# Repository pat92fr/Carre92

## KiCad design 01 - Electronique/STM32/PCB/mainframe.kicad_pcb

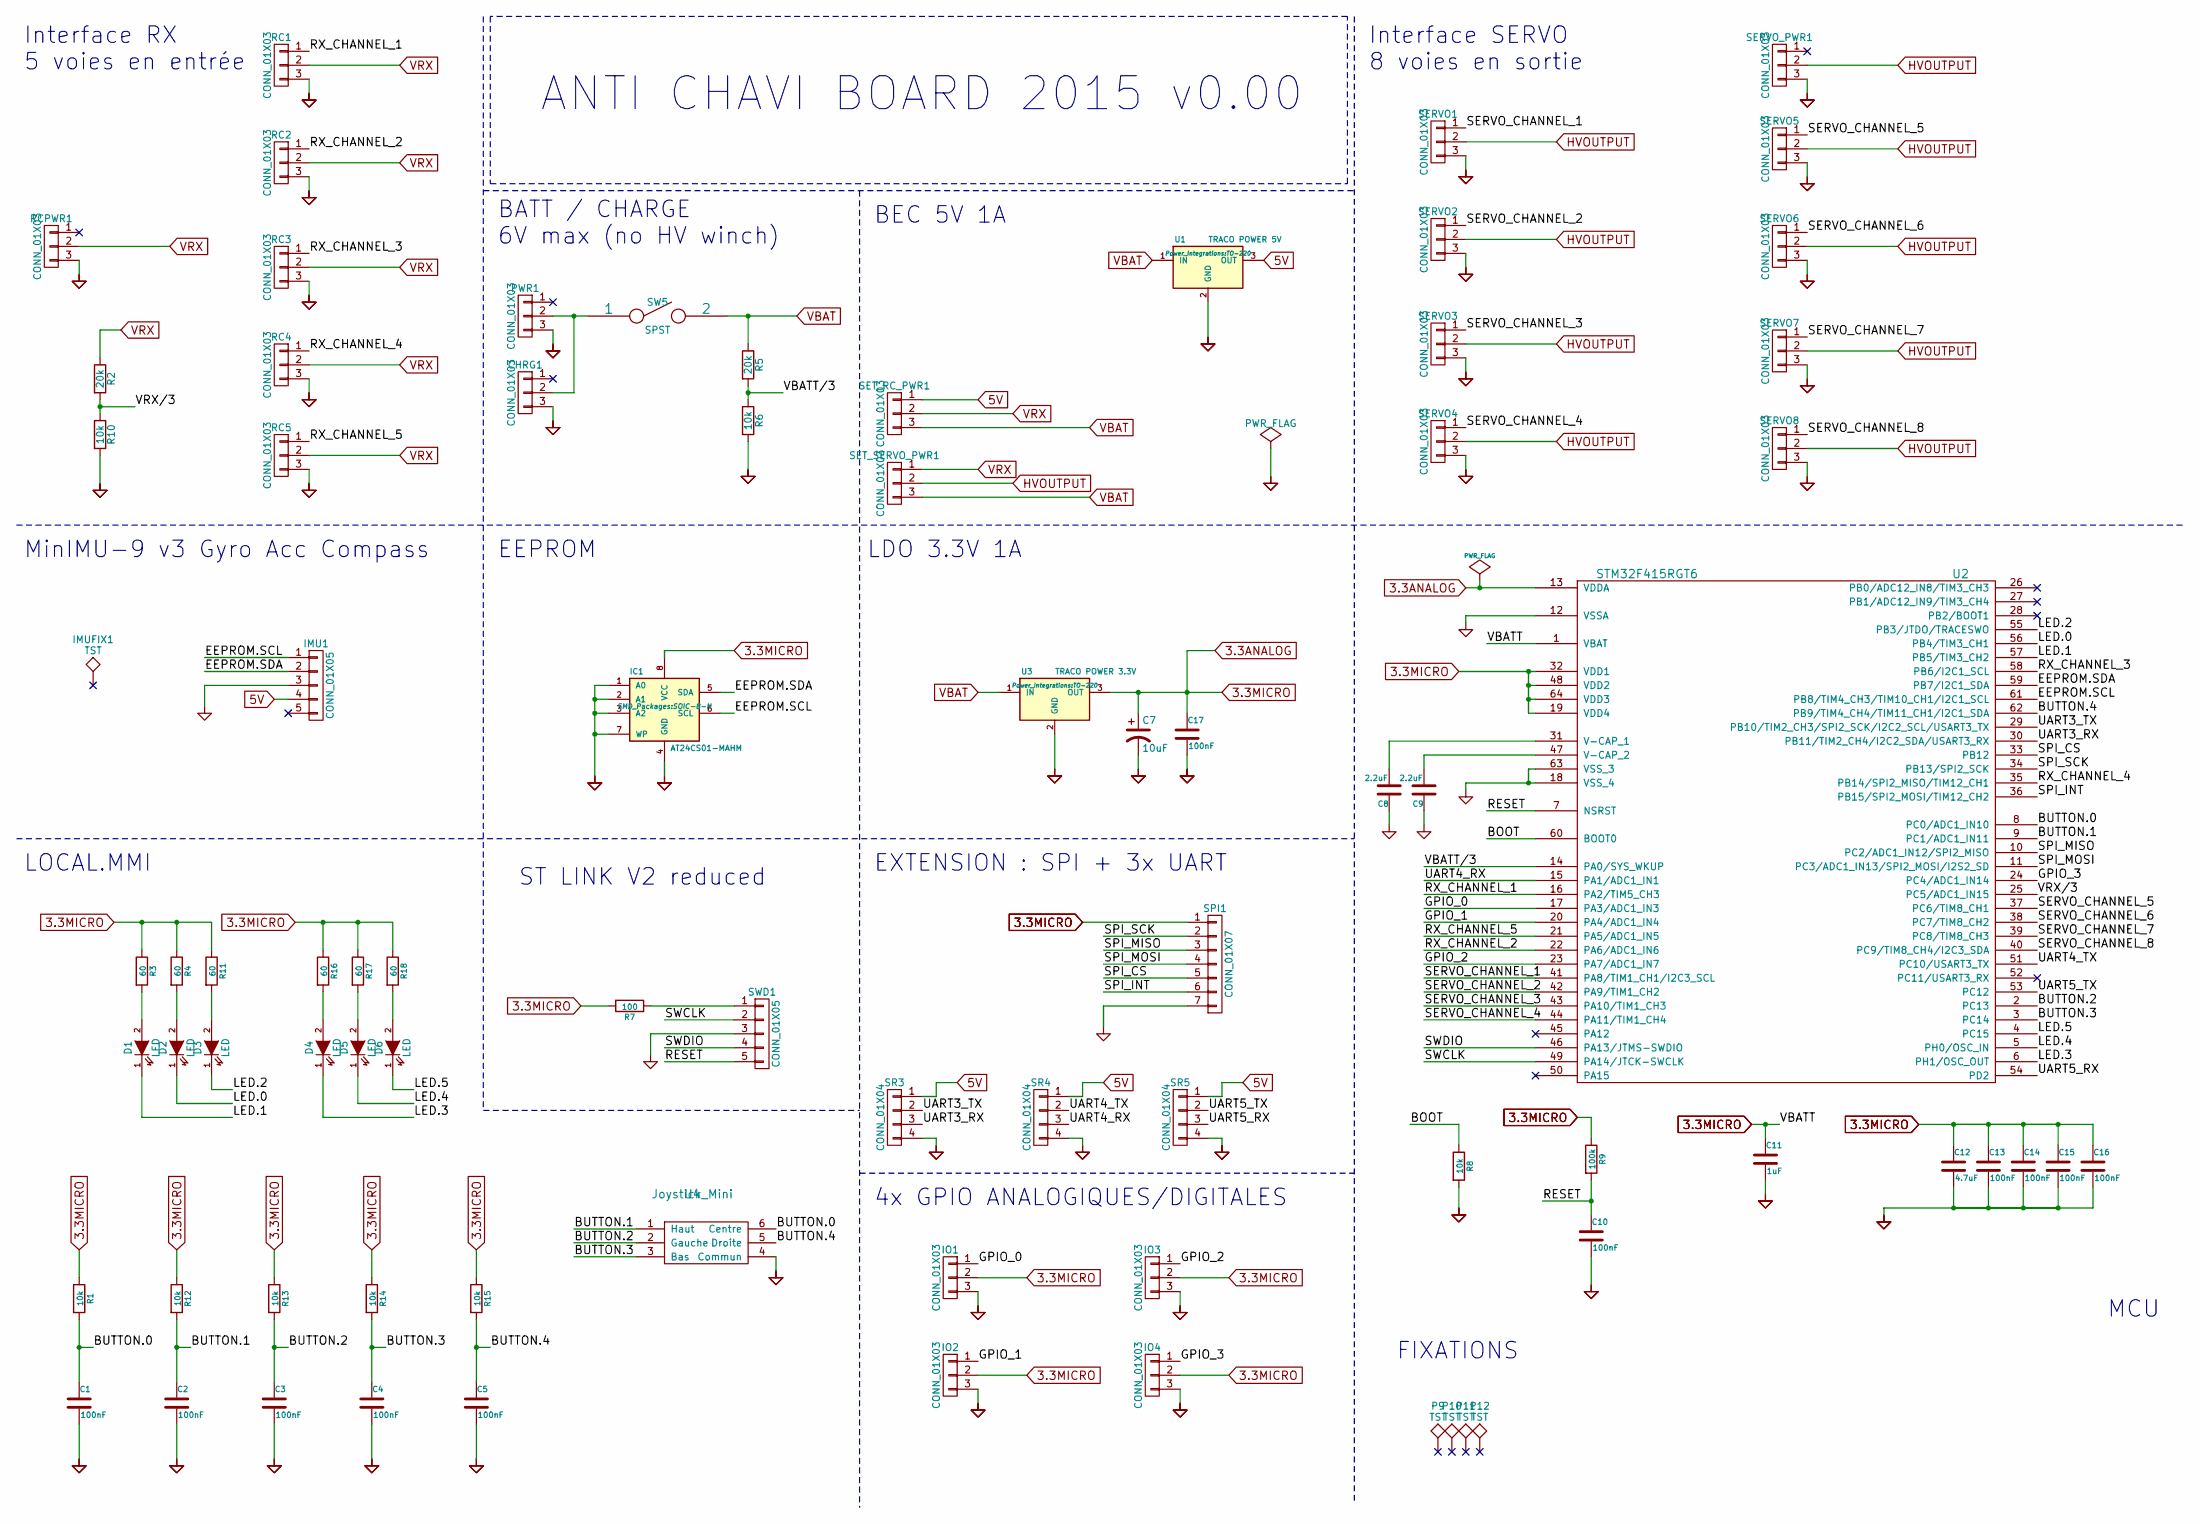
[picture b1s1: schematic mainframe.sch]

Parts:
C1, C2, C3, C4, C5, C10, C13, C14, C15, C16, C17: 100nF; C_0603_HandSoldering
C7: 10uF; C_0805_HandSoldering
C8, C9: 2.2uF; C_0603_HandSoldering
C11: 1uF; C_0603_HandSoldering
C12: 4.7uF; C_0603_HandSoldering
CHRG1: CONN_01X03; Pin_Header_Straight_1x03
D1, D2, D3, D4, D5, D6: LED; LED-0805
IC1: AT24CS01-MAHM; SOIC-8-N
IMU1: CONN_01X05; Pin_Header_Straight_1x05
IMUFIX1: TST; 1pin
IO1, IO2, IO3, IO4: CONN_01X03; Pin_Header_Straight_1x03
P9, P10, P11, P12: TST; 1pin
PWR1: CONN_01X03; Pin_Header_Straight_1x03
R1, R6, R8, R10, R12, R13, R14, R15: 10k; R_0603_HandSoldering
R2, R5: 20k; R_0603_HandSoldering
R3, R4, R11, R16, R17, R18: 60; R_0603_HandSoldering
R7: 100; R_0603_HandSoldering
R9: 100k; R_0603_HandSoldering
RC1, RC2, RC3, RC4, RC5: CONN_01X03; Pin_Header_Straight_1x03
RCPWR1: CONN_01X03; Pin_Header_Straight_1x03
SERVO1, SERVO2, SERVO3, SERVO4, SERVO5, SERVO6, SERVO7, SERVO8: CONN_01X03; Pin_Header_Straight_1x03
SERVO_PWR1: CONN_01X03; Pin_Header_Straight_1x03
SET_RC_PWR1: CONN_01X03; Pin_Header_Straight_1x03
SET_SERVO_PWR1: CONN_01X03; Pin_Header_Straight_1x03
SPI1: CONN_01X07; Pin_Header_Straight_1x07
SR3, SR4, SR5: CONN_01X04; Pin_Header_Straight_1x04
SW5: SPST; Pin_Header_Straight_1x02
SWD1: CONN_01X05; Pin_Header_Straight_1x05
U1: TRACO POWER 5V; TO-220
U2: STM32F415RGT6; LQFP-64_10x10mm_Pitch0.5mm
U3: TRACO POWER 3.3V; TO-220
U4: Joystick_Mini

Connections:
3.3ANALOG: C7.1, C11.1, C12.1, C13.1, C14.1, C15.1, C16.1, C17.1, IC1.8 (VCC), IO1.2, IO2.2, IO3.2, IO4.2, R1.1, R3.1, R4.1, R7.2, R9.1, R11.1, R12.1, R13.1, R14.1, R15.1, R16.1, R17.1, R18.1, SPI1.1, U2.1 (VBAT), U2.13 (VDDA), U2.19 (VDD4), U2.32 (VDD1), U2.48 (VDD2), U2.64 (VDD3), U3.3 (OUT)
5V: IMU1.4, SET_RC_PWR1.1, SR3.1, SR4.1, SR5.1, U1.3 (OUT)
/BOOT: R8.1, U2.60 (BOOT0)
/BUTTON.0: C1.1, R1.2, U2.8 (PC0/ADC1_IN10), U4.6 (Centre)
/BUTTON.1: C2.1, R12.2, U2.9 (PC1/ADC1_IN11), U4.1 (Haut)
/BUTTON.2: C3.1, R13.2, U2.2 (PC13), U4.2 (Gauche)
/BUTTON.3: C4.1, R14.2, U2.3 (PC14), U4.3 (Bas)
/BUTTON.4: C5.1, R15.2, U2.62 (PB9/TIM4_CH4/TIM11_CH1/I2C1_SDA), U4.5 (Droite)
/EEPROM.SCL: IC1.6 (SCL), IMU1.1, U2.61 (PB8/TIM4_CH3/TIM10_CH1/I2C1_SCL)
/EEPROM.SDA: IC1.5 (SDA), IMU1.2, U2.59 (PB7/I2C1_SDA)
/GPIO_0: IO1.1, U2.17 (PA3/ADC1_IN3)
/GPIO_1: IO2.1, U2.20 (PA4/ADC1_IN4)
/GPIO_2: IO3.1, U2.23 (PA7/ADC1_IN7)
/GPIO_3: IO4.1, U2.24 (PC4/ADC1_IN14)
/LED.0: D2.1 (K), U2.56 (PB4/TIM3_CH1)
/LED.1: D1.1 (K), U2.57 (PB5/TIM3_CH2)
/LED.2: D3.1 (K), U2.55 (PB3/JTDO/TRACESWO)
/LED.3: D4.1 (K), U2.6 (PH1/OSC_OUT)
/LED.4: D5.1 (K), U2.5 (PH0/OSC_IN)
/LED.5: D6.1 (K), U2.4 (PC15)
/RESET: C10.1, R9.2, SWD1.5, U2.7 (NSRST)
/RX_CHANNEL_1: RC1.1, U2.16 (PA2/TIM5_CH3)
/RX_CHANNEL_2: RC2.1, U2.22 (PA6/ADC1_IN6)
/RX_CHANNEL_3: RC3.1, U2.58 (PB6/I2C1_SCL)
/RX_CHANNEL_4: RC4.1, U2.35 (PB14/SPI2_MISO/TIM12_CH1)
/RX_CHANNEL_5: RC5.1, U2.21 (PA5/ADC1_IN5)
/SERVO_CHANNEL_1: SERVO1.1, U2.41 (PA8/TIM1_CH1/I2C3_SCL)
/SERVO_CHANNEL_2: SERVO2.1, U2.42 (PA9/TIM1_CH2)
/SERVO_CHANNEL_3: SERVO3.1, U2.43 (PA10/TIM1_CH3)
/SERVO_CHANNEL_4: SERVO4.1, U2.44 (PA11/TIM1_CH4)
/SERVO_CHANNEL_5: SERVO5.1, U2.37 (PC6/TIM8_CH1)
/SERVO_CHANNEL_6: SERVO6.1, U2.38 (PC7/TIM8_CH2)
/SERVO_CHANNEL_7: SERVO7.1, U2.39 (PC8/TIM8_CH3)
/SERVO_CHANNEL_8: SERVO8.1, U2.40 (PC9/TIM8_CH4/I2C3_SDA)
/SPI_CS: SPI1.5, U2.33 (PB12)
/SPI_INT: SPI1.6, U2.36 (PB15/SPI2_MOSI/TIM12_CH2)
/SPI_MISO: SPI1.3, U2.10 (PC2/ADC1_IN12/SPI2_MISO)
/SPI_MOSI: SPI1.4, U2.11 (PC3/ADC1_IN13/SPI2_MOSI/I2S2_SD)
/SPI_SCK: SPI1.2, U2.34 (PB13/SPI2_SCK)
/SWCLK: SWD1.2, U2.49 (PA14/JTCK-SWCLK)
/SWDIO: SWD1.4, U2.46 (PA13/JTMS-SWDIO)
/UART3_RX: SR3.3, U2.30 (PB11/TIM2_CH4/I2C2_SDA/USART3_RX)
/UART3_TX: SR3.2, U2.29 (PB10/TIM2_CH3/SPI2_SCK/I2C2_SCL/USART3_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)
/UART4_RX: SR4.3, U2.15 (PA1/ADC1_IN1)
/UART4_TX: SR4.2, U2.51 (PC10/USART3_TX)
/UART5_RX: SR5.3, U2.54 (PD2)
/UART5_TX: SR5.2, U2.53 (PC12)
/VBATT/3: R5.2, R6.1, U2.14 (PA0/SYS_WKUP)
/VRX/3: R2.2, R10.1, U2.25 (PC5/ADC1_IN15)
GND: C1.2, C2.2, C3.2, C4.2, C5.2, C7.2, C8.1, C9.1, C10.2, C11.2, C12.2, C13.2, C14.2, C15.2, C16.2, C17.2, CHRG1.3, IC1.1 (A0), IC1.2 (A1), IC1.3 (A2), IC1.4 (GND), IC1.7 (WP), IMU1.3, IO1.3, IO2.3, IO3.3, IO4.3, PWR1.3, R6.2, R8.2, R10.2, RC1.3, RC2.3, RC3.3, RC4.3, RC5.3, RCPWR1.3, SERVO1.3, SERVO2.3, SERVO3.3, SERVO4.3, SERVO5.3, SERVO6.3, SERVO7.3, SERVO8.3, SERVO_PWR1.3, SPI1.7, SR3.4, SR4.4, SR5.4, SWD1.3, U1.2 (GND), U2.12 (VSSA), U2.18 (VSS_4), U2.63 (VSS_3), U3.2 (GND), U4.4 (Commun)
HVOUTPUT: SERVO1.2, SERVO2.2, SERVO3.2, SERVO4.2, SERVO5.2, SERVO6.2, SERVO7.2, SERVO8.2, SERVO_PWR1.2, SET_SERVO_PWR1.2
unnamed: C8.2, U2.31 (V-CAP_1)
unnamed: C9.2, U2.47 (V-CAP_2)
unnamed: CHRG1.2, PWR1.2, SW5.1
unnamed: D1.2 (A), R3.2
unnamed: D2.2 (A), R4.2
unnamed: D3.2 (A), R11.2
unnamed: D4.2 (A), R16.2
unnamed: D5.2 (A), R17.2
unnamed: D6.2 (A), R18.2
unnamed: R7.1, SWD1.1
VBAT: R5.1, SET_RC_PWR1.3, SET_SERVO_PWR1.3, SW5.2, U1.1 (IN), U3.1 (IN)
VRX: R2.1, RC1.2, RC2.2, RC3.2, RC4.2, RC5.2, RCPWR1.2, SET_RC_PWR1.2, SET_SERVO_PWR1.1

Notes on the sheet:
MinIMU-9 v3 Gyro Acc Compass
LOCAL.MMI
EEPROM
MCU
ST LINK V2 reduced
ANTI CHAVI BOARD 2015 v0.00
BATT / CHARGE 6V max (no HV winch)
Interface RX 5 voies en entrée
Interface SERVO 8 voies en sortie
EXTENSION : SPI + 3x UART
4x GPIO ANALOGIQUES/DIGITALES
FIXATIONS
BEC 5V 1A
LDO 3.3V 1A

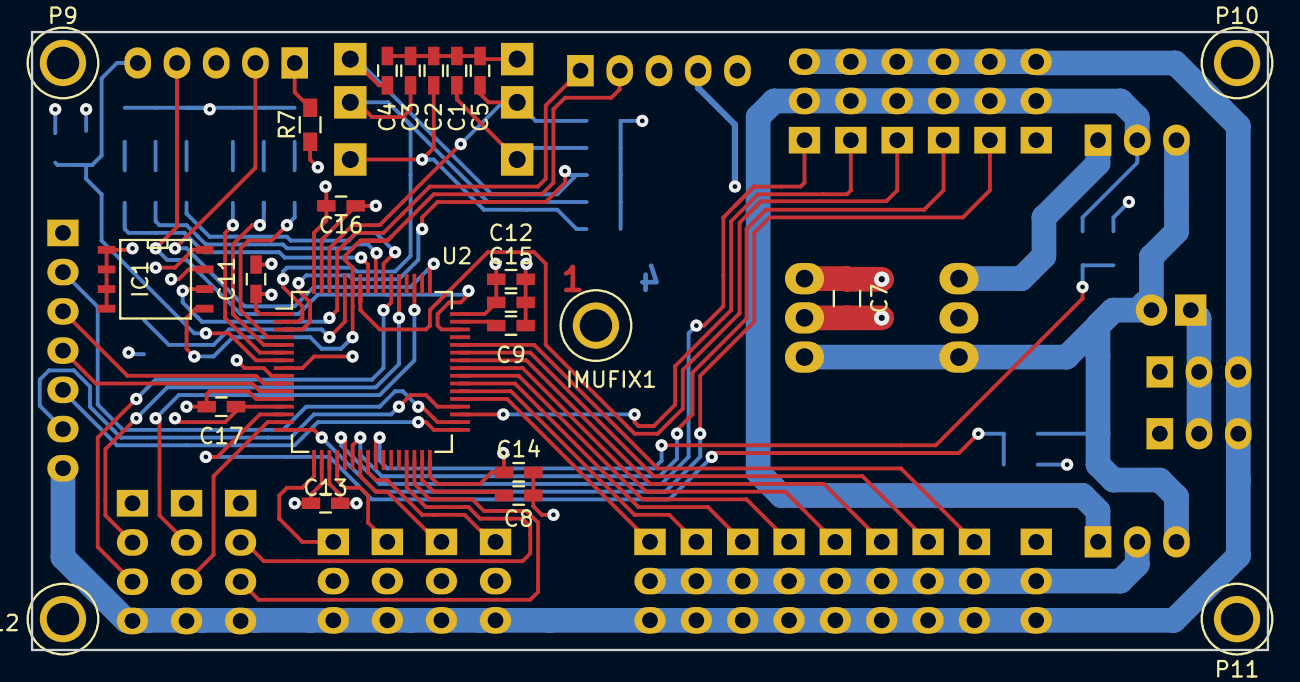
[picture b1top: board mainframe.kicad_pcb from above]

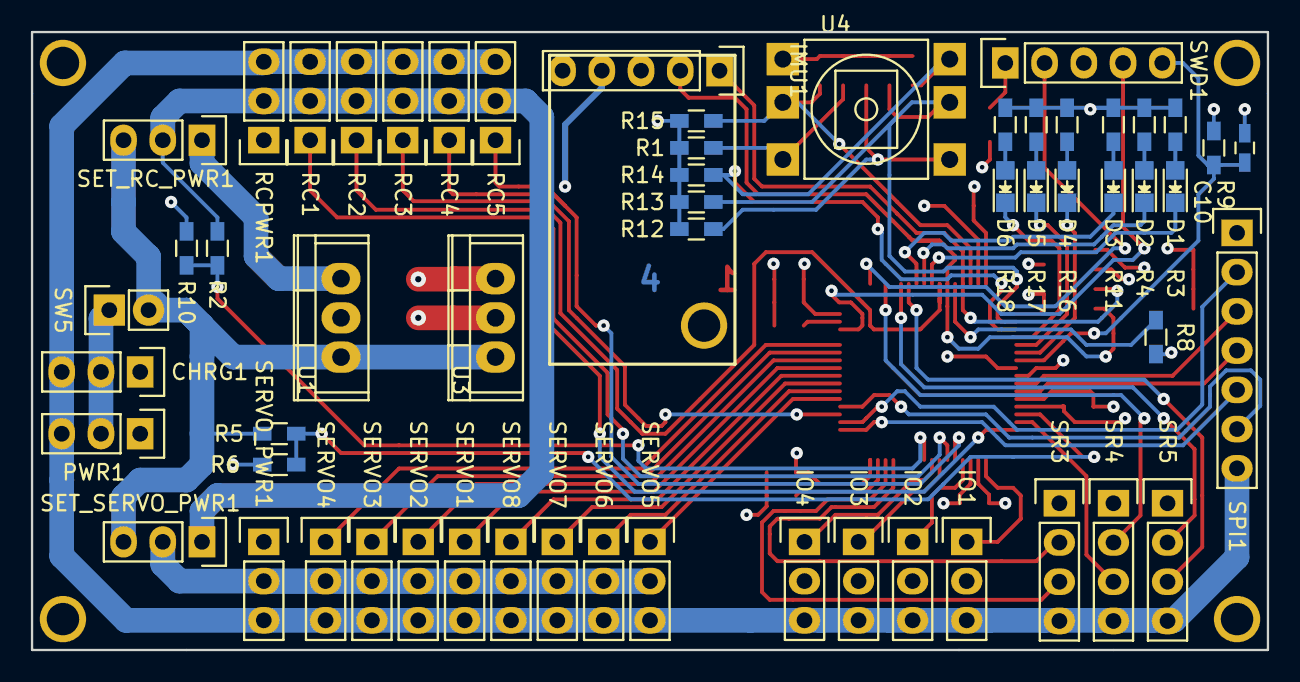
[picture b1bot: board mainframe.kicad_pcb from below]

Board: 4 copper layers, 80.0 x 40.0 mm, 80 parts (57 on the bottom side), 63 nets.

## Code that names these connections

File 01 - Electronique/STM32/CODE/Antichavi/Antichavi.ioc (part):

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Mcu.Name=STM32F415RGTx
Mcu.Package=LQFP64
Mcu.UserName=STM32F415RGTx
PA0-WKUP.GPIOParameters=GPIO_Label
PA0-WKUP.GPIO_Label=VBATT_DIV_3
PA0-WKUP.Signal=ADCx_IN0
PA1.Mode=Asynchronous
PA1.Signal=UART4_RX
PA10.GPIOParameters=GPIO_Label
PA10.GPIO_Label=SERVO_CHANNEL_3
PA10.Signal=S_TIM1_CH3
PA11.GPIOParameters=GPIO_Label
PA11.GPIO_Label=SERVO_CHANNEL_4
PA11.Signal=S_TIM1_CH4
PA13.Mode=Serial-Wire
PA13.Signal=SYS_JTMS-SWDIO
PA14.Mode=Serial-Wire
PA14.Signal=SYS_JTCK-SWCLK
PA2.GPIOParameters=GPIO_Label
PA2.GPIO_Label=RX_CHANNEL_1
PA2.Signal=S_TIM9_CH1
PA3.GPIOParameters=GPIO_Label
PA3.GPIO_Label=GPIO_0
PA3.Signal=GPIO_Input
PA4.GPIOParameters=GPIO_Label
PA4.GPIO_Label=GPIO_4
PA4.Signal=GPIO_Input
PA5.GPIOParameters=GPIO_Label
PA5.GPIO_Label=RX_CHANNEL_5
PA5.Signal=S_TIM2_CH1_ETR
PA6.GPIOParameters=GPIO_Label
PA6.GPIO_Label=RX_CHANNEL_2
PA6.Signal=S_TIM3_CH1
PA7.GPIOParameters=GPIO_Label
PA7.GPIO_Label=GPIO_2
PA7.Signal=GPIO_Input
PA8.GPIOParameters=GPIO_Label
PA8.GPIO_Label=SERVO_CHANNEL_1
PA8.Signal=S_TIM1_CH1
PA9.GPIOParameters=GPIO_Label
PA9.GPIO_Label=SERVO_CHANNEL_2
PA9.Signal=S_TIM1_CH2
PB10.Mode=Asynchronous
PB10.Signal=USART3_TX
PB11.Mode=Asynchronous
PB11.Signal=USART3_RX
PB12.GPIOParameters=GPIO_Label
PB12.GPIO_Label=SPI_CS
PB12.Signal=GPIO_Output
PB13.Mode=Full_Duplex_Master
PB13.Signal=SPI2_SCK
PB14.GPIOParameters=GPIO_Label
PB14.GPIO_Label=RX_CHANNEL_4
PB14.Signal=S_TIM12_CH1
PB15.GPIOParameters=GPIO_Label
PB15.GPIO_Label=SPI_INT
PB15.Signal=GPXTI15
PB3.GPIOParameters=GPIO_Label
PB3.GPIO_Label=LED2
PB3.Signal=GPIO_Output
PB4.GPIOParameters=GPIO_Label
PB4.GPIO_Label=LED0
PB4.Signal=GPIO_Output
PB5.GPIOParameters=GPIO_Label
PB5.GPIO_Label=LED1
PB5.Signal=GPIO_Output
PB6.GPIOParameters=GPIO_Label
PB6.GPIO_Label=RX_CHANNEL_3
PB6.Signal=S_TIM4_CH1
PB7.Mode=I2C
PB7.Signal=I2C1_SDA
PB8.Mode=I2C
PB8.Signal=I2C1_SCL
PB9.GPIOParameters=GPIO_Label
PB9.GPIO_Label=BUTTON_4
PB9.Signal=GPXTI9
PC0.GPIOParameters=GPIO_Label
PC0.GPIO_Label=BUTTON_0
PC0.Signal=GPXTI0
PC1.GPIOParameters=GPIO_Label
PC1.GPIO_Label=BUTTON_1
PC1.Signal=GPXTI1
PC10.Mode=Asynchronous
PC10.Signal=UART4_TX
PC12.Mode=Asynchronous
PC12.Signal=UART5_TX
PC13-ANTI_TAMP.GPIOParameters=GPIO_Label
PC13-ANTI_TAMP.GPIO_Label=BUTTON_2
PC13-ANTI_TAMP.Signal=GPXTI13
PC14-OSC32_IN.GPIOParameters=GPIO_Label
PC14-OSC32_IN.GPIO_Label=BUTTON_3
PC14-OSC32_IN.Signal=GPXTI14
PC15-OSC32_OUT.GPIOParameters=GPIO_Label
PC15-OSC32_OUT.GPIO_Label=LED5
PC15-OSC32_OUT.Signal=GPIO_Output
PC2.Mode=Full_Duplex_Master
PC2.Signal=SPI2_MISO
PC3.Mode=Full_Duplex_Master
PC3.Signal=SPI2_MOSI
PC4.GPIOParameters=GPIO_Label
PC4.GPIO_Label=GPIO_3
PC4.Signal=GPIO_Input
PC5.GPIOParameters=GPIO_Label
PC5.GPIO_Label=VRX_DIV_3
PC5.Signal=ADCx_IN15
PC6.GPIOParameters=GPIO_Label
PC6.GPIO_Label=SERVO_CHANNEL_5
PC6.Signal=S_TIM8_CH1
PC7.GPIOParameters=GPIO_Label
PC7.GPIO_Label=SERVO_CHANNEL_6
PC7.Signal=S_TIM8_CH2
PC8.GPIOParameters=GPIO_Label
PC8.GPIO_Label=SERVO_CHANNEL_7
PC8.Signal=S_TIM8_CH3
PC9.GPIOParameters=GPIO_Label
PC9.GPIO_Label=SERVO_CHANNEL_8
PC9.Signal=S_TIM8_CH4
PD2.Mode=Asynchronous
PD2.Signal=UART5_RX
PH0-OSC_IN.GPIOParameters=GPIO_Label
PH0-OSC_IN.GPIO_Label=LED4
PH0-OSC_IN.Signal=GPIO_Output
PH1-OSC_OUT.GPIOParameters=GPIO_Label
PH1-OSC_OUT.GPIO_Label=LED3
PH1-OSC_OUT.Signal=GPIO_Output
RCC.HSE_VALUE=25000000
RCC.SYSCLKFreq_VALUE=168000000
RCC.SYSCLKSource=RCC_SYSCLKSOURCE_PLLCLK
board=Antichavi
boardIOC=true

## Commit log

2019-07-18 AIv1
2019-07-19 Serial Code
2019-07-19 Example IA
2019-07-19 STM32F415_ctrl
2019-07-19 servo INV
2019-07-19 RX CH1 CH2 bypass OK
2019-07-19 Commutation A/M
2019-07-19 RX circular FIX
2019-07-20 FSM add
2019-07-20 PWM Input capture filter FIX + BT_COM
2019-07-20 Coffret Ctrl
2019-07-21 Coffret Ctrl MAJ
2019-07-23 logo
2019-07-24 AI V2
2019-07-25 CNN linear
2019-07-25 AI2 test 3 bitume
2019-07-26 test4 bitume
2019-07-27 CNN up
2019-07-28 CNN v2 MAJ
2019-07-28 AIv2 Bitume MAJ
2019-07-28 Script de génération du dataset
    Script de génération du dataset et photos de fond
2019-07-29 Update GenereImages.py
    Modification de l'arborescence du dataset : un répertoire par image de fond puis 1 répertoire par angle d'orientation de la ligne.
    Sinon, plusieurs centaines de milliers de fichiers dans un répertoire, c'est difficile à gérer !
2019-07-29 Update GenereImages.py
    Modification des répertoires pour stocker les images
2019-07-30 AI v2 Vizu
2019-07-30 Update GenereImages.py
    Optimisation et parallélisation des calculs.
    Calcule le nombre de coeurs (OK sous Windows, pour linuxn modifier les lignes 132-135) et lance n calculs en parallèle.
2019-07-30 IA v2
2019-07-31 cli test
2019-07-31 BackUp rover
2019-08-01 Full CONV test
2019-08-07 test CLI
2019-08-07 STM32 direction active AI
2019-08-07 STM32 RC start AI (robust)
2019-08-07 Alain V2
2019-08-08 Alain Fond
2019-08-08 Alain script
2019-08-08 fonds
2019-08-09 Benjamin
2019-08-09 IAv3
2019-08-09 CleanUP
2019-08-09 Pipeline
2019-08-09 Predict
2019-08-11 datagenerator
2019-08-11 Pipeline no more X Y dataset file
2019-08-11 Pipeline v1 ok
2019-08-12 Dataset prédiction
2019-08-12 Buggy
2019-08-13 ANN prediction
2019-08-13 tt01
2019-08-14 Prediction
2019-08-15 Camera v2 avec Buggy server et client update
2019-08-15 client
2019-08-15 Notes démarrage Jetson
    Quelques notes sur l'optimisation du temps de démarrage et comment lancer un script automatiquement et le plus tôt possible.
2019-08-16 PCB upload
2019-08-16 STM32 Soft : ajout des lidars
2019-08-16 STM32
2019-08-17 STM32
    Permutation des UART. Ne marche pas mieux. Time out 3 seconde coté Python.
2019-08-17 STM32 fix IRQ
    Correction inversion UART LiD et LiG
2019-08-17 STM32 refactoring
    types, enum, telemetry stop and wait,
    fix on Telemetry frame reply per AI frame
2019-08-17 test serial comm between jetson and STM32
2019-08-17 LIDAR OK REady for PID with Jetson
2019-08-19 Lidar PID
2019-08-20 Telemetry et PID Wall
2019-08-20 Config file buggy
2019-08-20 prediction 5x5x1
2019-08-21 PID simplification
2019-08-21 Buggy client server ( Bernard v1 )
2019-08-21 Reglages mono PID, vitesse manuelle
2019-08-21 TODOs
2019-08-22 Ajout START/STOP
2019-08-22 Stupid speed regulation in AUTO mode
2019-08-22 Speed improvement
2019-08-22 todo
2019-08-22 Telemetry
2019-08-23 Régulation de vitesse et dual rate direction
2019-08-23 Telemetry merge
2019-08-23 Essais avec telemetry et télécommande, probleme de trim dierction
    ajouter configuraztion des trim et du dual rate
2019-08-24 clean up
2019-08-24 crontab
2019-08-24 params
2019-08-24 trim et dual rate en params
2019-08-24 Data logger
2019-08-25 Third LIDAR code
2019-08-25 Video capture
2019-08-25 3DCNN
2019-08-26 LIDAR3
2019-08-26 LIDAR3 OK
2019-08-26 START OK
2019-08-27 START
2019-08-28 [FGA] ajout télémétrie version 2
2019-08-28 Start button
2019-08-28 Start / Stop
2019-08-28 [FGA] MAJ télémétrie + ménage
2019-08-28 Ajout du log des infos de télémétrie en continue, même si on reste 3 heures à regarde une courbe
2019-08-28 Gearbox
2019-08-29 Ajout des paramètres --log pour créer le fichier de log et --duration pour modifier la fenêtre d'observation
2019-08-29 Terminé les CTRL C :angry: on a une vraie IHM maintenant :+1:
2019-08-29 Analyse Lidars
2019-08-30 Ajout du bouton stop/go pour arreter la prise de trace
2019-08-31 Photos fonds
2019-08-31 Create 03 - Train CNN v3.07a.py
    Train CNN
2019-09-02 Local Dataset Recording
2019-09-02 Telemetry client sorted
2019-09-02 Mise à jour
2019-09-02 Beautiffulage
2019-09-04 Tlemetry Speed
2019-09-04 3D CNN Predict
2019-09-04 STM32_vitesse
2019-09-04 STM32_distance
2019-09-05 3DCN DonkeyCAr
2019-09-05 3D CNN
2019-09-06 Buggy Update PID SPEED
2019-09-06 Dataset 004
2019-09-07 3DCNN tools update
2019-09-07 3DCNN update
2019-09-07 3D CNN rework + notice
2019-09-07 3D CNN update
2019-09-07 Circuit OBJ mesh w/o UVtext
2019-09-07 Circuit
2019-09-07 Circuit OBJ
2019-09-08 Simulator
2019-09-08 Simulator upgrade
2019-09-08 simulator update
2019-09-09 platine et hall
2019-09-09 3DCNN dans simulator
2019-09-10 Batchnorm conv3D + Réduction CNN + AI dans simulator
2019-09-10 PID vitesse avec Kff
2019-09-10 3DCNN one output
2019-09-11 3DCNN lne
2019-09-11 buggy update
2019-09-11 2D CNN simple et efficace
2019-09-12 3D CNN paul
2019-09-12 2D CNN paul
2019-09-13 PID LINE
2019-09-13 2D CNN
2019-09-13 2D CNN Paul OKKKK
2019-09-14 Clean Up & versionning
2019-09-14 CNN update
2019-09-15 Clean-up
2019-09-15 Adding arch to circuit
2019-09-15 circuit update
2019-09-15 circuit clean up
2019-09-15 Dataset 009
2019-09-16 Support incliné LIDAR
2019-09-16 Support Camera
2019-09-16 Meca update, pipeline update test set, simulator media update
2019-09-17 Casquette
2019-09-18 Simulator update (menu)
2019-09-19 Simulator PhysX
2019-09-20 Param update
2019-09-20 Simulator adding keyboard control and speed PID like a robot
2019-09-21 Simulator (robust settings)
2019-09-21 Simulator adding 2D cross for AI prediction
2019-09-21 Simulator (same controller as buggy)
2019-09-21 Simulator (full pipeline and circuit test) OK
    train_and_valid_dataset_list = [ "dataset_005", "dataset_009", "dataset_011", "dataset_012" ]
    # CNN parameters
    layers = [
    ('crop2D', 26), ## do not change
    ('norm', 0), ## do not change
    ('conv2D', 8, (5,5), (2,2),'relu'), ## filters, kernel_size, stride, activation
2019-09-21 Simulateur (sliders)
2019-09-21 Simulator (all sliders)
2019-09-22 Simulator (adding telemetry support emulation)
2019-09-22 Simulator (réglage PID et debug avec télémétrie)
2019-09-23 Simulator (lap timer)
2019-09-23 Buggy BkUp
2019-09-23 Simulator to Buggy Synch
2019-09-23 Simulator (LIDAR PID)
2019-09-24 Simulator (blending)
2019-09-24 Simulateur (clean uping)
2019-09-25 Simulator (blending + strategy)
2019-09-25 Simulator to Buggy
2019-09-28 Simulator carthographe
2019-10-01 MLC failure
2019-10-02 bkup
2019-10-02 Liste
2019-10-04 Toulouse bkup
2019-10-04 Toulouse max speed
2019-10-04 Toulouse final release essais
2019-10-05 Frein
2019-10-05 NeuNoeil1_Sans_IA
2019-10-05 Finale
2019-10-07 Finale Toulouse 2019
2019-10-13 ToulouseRobotRace Last Test
2019-10-30 [FGA] ajout du serveur télémtrie carto : buggy et PC
2019-11-09 [FGA] ajout de l'optim python zmq
2019-11-09 [FGA] ajout de la synchronosation de fin d'execution
2019-11-10 [FGA] beautifullage
